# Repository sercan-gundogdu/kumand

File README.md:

# kumand [discontinued*]
Kumand is a low-power user-configurable remote controller device for personal computers, working on WLAN, allowing to manipulate every single media tool that has functionality to operate with keyboard shortcuts/hotkeys by emulating keystrokes determined in selected profile.

*The project is discontinued because the ESP8266 SoC does not meet the project's requirements in the aspect of power consumption and connectivity speed, it seems that ESP8266 has no proper sleep functionality to implement. The project will be redesigned with appropriate connectivity IC and MCU.

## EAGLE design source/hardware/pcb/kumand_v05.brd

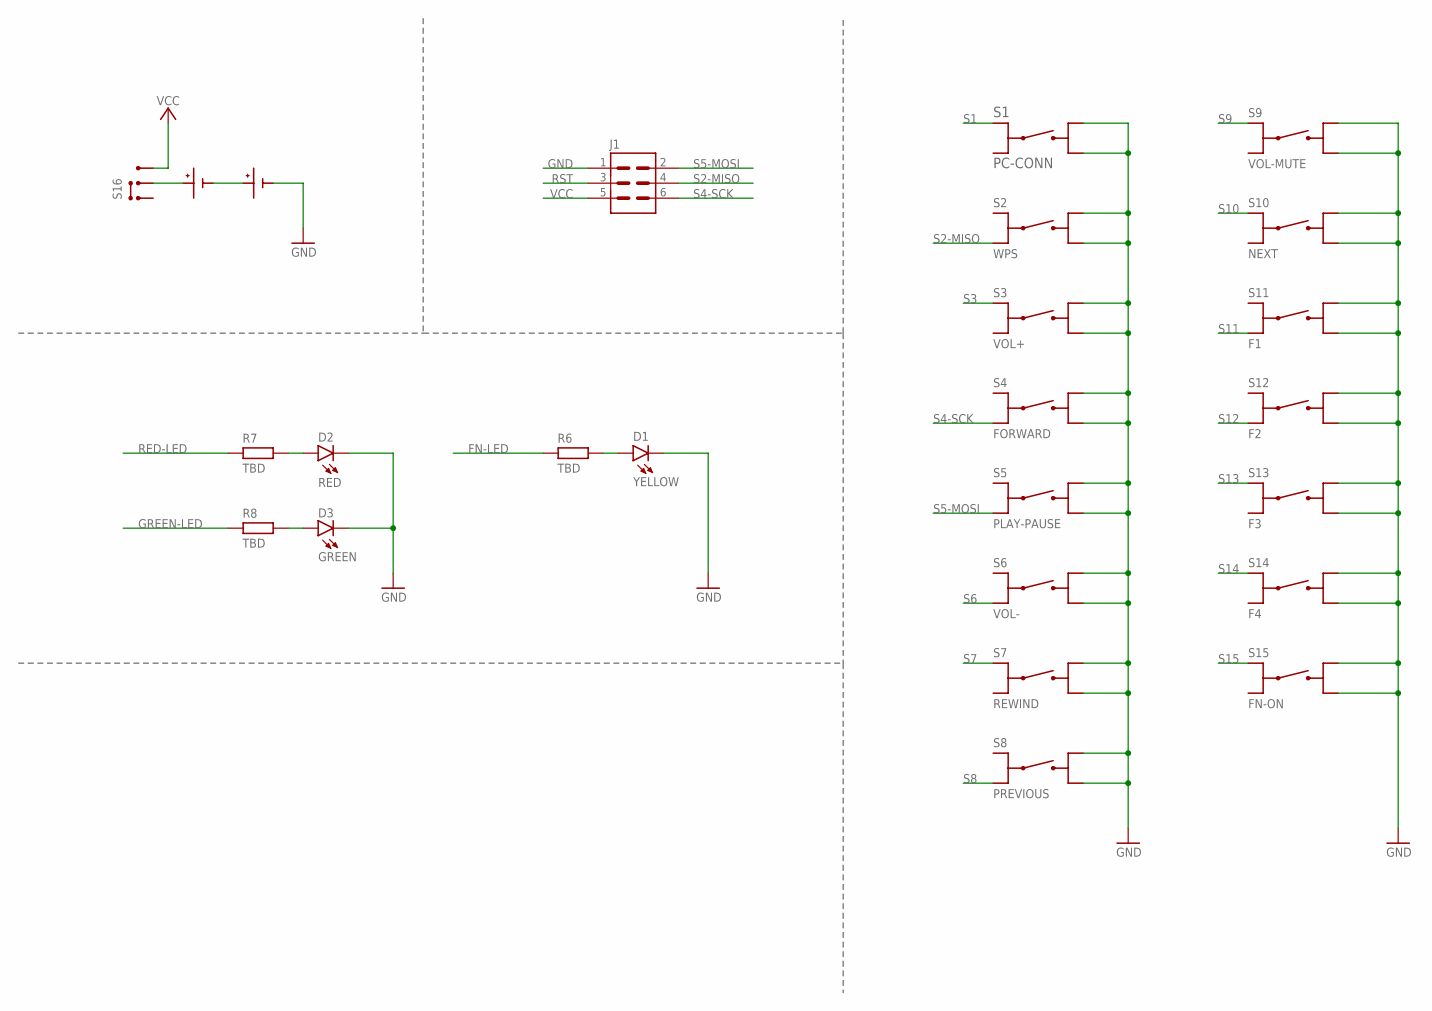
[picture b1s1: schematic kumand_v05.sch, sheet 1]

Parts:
D1: YELLOW; LED-1206
D2: RED; LED-1206
D3: GREEN; LED-1206
J1: 3X2-SMD-DOT
R6, R7, R8: TBD; R1206
S1: PC-CONN; PTS525
S2: WPS; PTS525
S3: VOL+; PTS525
S4: FORWARD; PTS525
S5: PLAY-PAUSE; PTS525
S6: VOL-; PTS525
S7: REWIND; PTS525
S8: PREVIOUS; PTS525
S9: VOL-MUTE; PTS525
S10: NEXT; PTS525
S11: F1; PTS525
S12: F2; PTS525
S13: F3; PTS525
S14: F4; PTS525
S15: FN-ON; PTS525
S16: CL-SB-12B-02T; CL-SB-12B-02T-PACKAGE
U$4, U$5: BK-82-DEVICE; BK-82-PACKAGE

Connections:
FN-LED: R6.2; also elsewhere on the board
GND: D1.C, D2.C, D3.C, J1.1, S1.3, S1.4, S2.3, S2.4, S3.3, S3.4, S4.3, S4.4, S5.3, S5.4, S6.3, S6.4, S7.3, S7.4, S8.3, S8.4, S9.3, S9.4, S10.3, S10.4, S11.3, S11.4, S12.3, S12.4, S13.3, S13.4, S14.3, S14.4, S15.3, S15.4, U$5.P$2, U$5.P$4; also elsewhere on the board
GREEN-LED: R8.2; also elsewhere on the board
unnamed: D1.A, R6.1
unnamed: U$4.P$2, U$4.P$4, U$5.P$1, U$5.P$3
unnamed: S16.P$2, U$4.P$1, U$4.P$3
unnamed: D2.A, R7.1
unnamed: D3.A, R8.1
RED-LED: R7.2; also elsewhere on the board
RST: J1.3; also elsewhere on the board
S1: S1.1; also elsewhere on the board
S2-MISO: J1.4, S2.2; also elsewhere on the board
S3: S3.1; also elsewhere on the board
S4-SCK: J1.6, S4.2; also elsewhere on the board
S5-MOSI: J1.2, S5.2; also elsewhere on the board
S6: S6.2; also elsewhere on the board
S7: S7.1; also elsewhere on the board
S8: S8.2; also elsewhere on the board
S9: S9.1; also elsewhere on the board
S10: S10.1; also elsewhere on the board
S11: S11.2; also elsewhere on the board
S12: S12.2; also elsewhere on the board
S13: S13.1; also elsewhere on the board
S14: S14.1; also elsewhere on the board
S15: S15.1; also elsewhere on the board
VCC: J1.5, S16.P$3; also elsewhere on the board

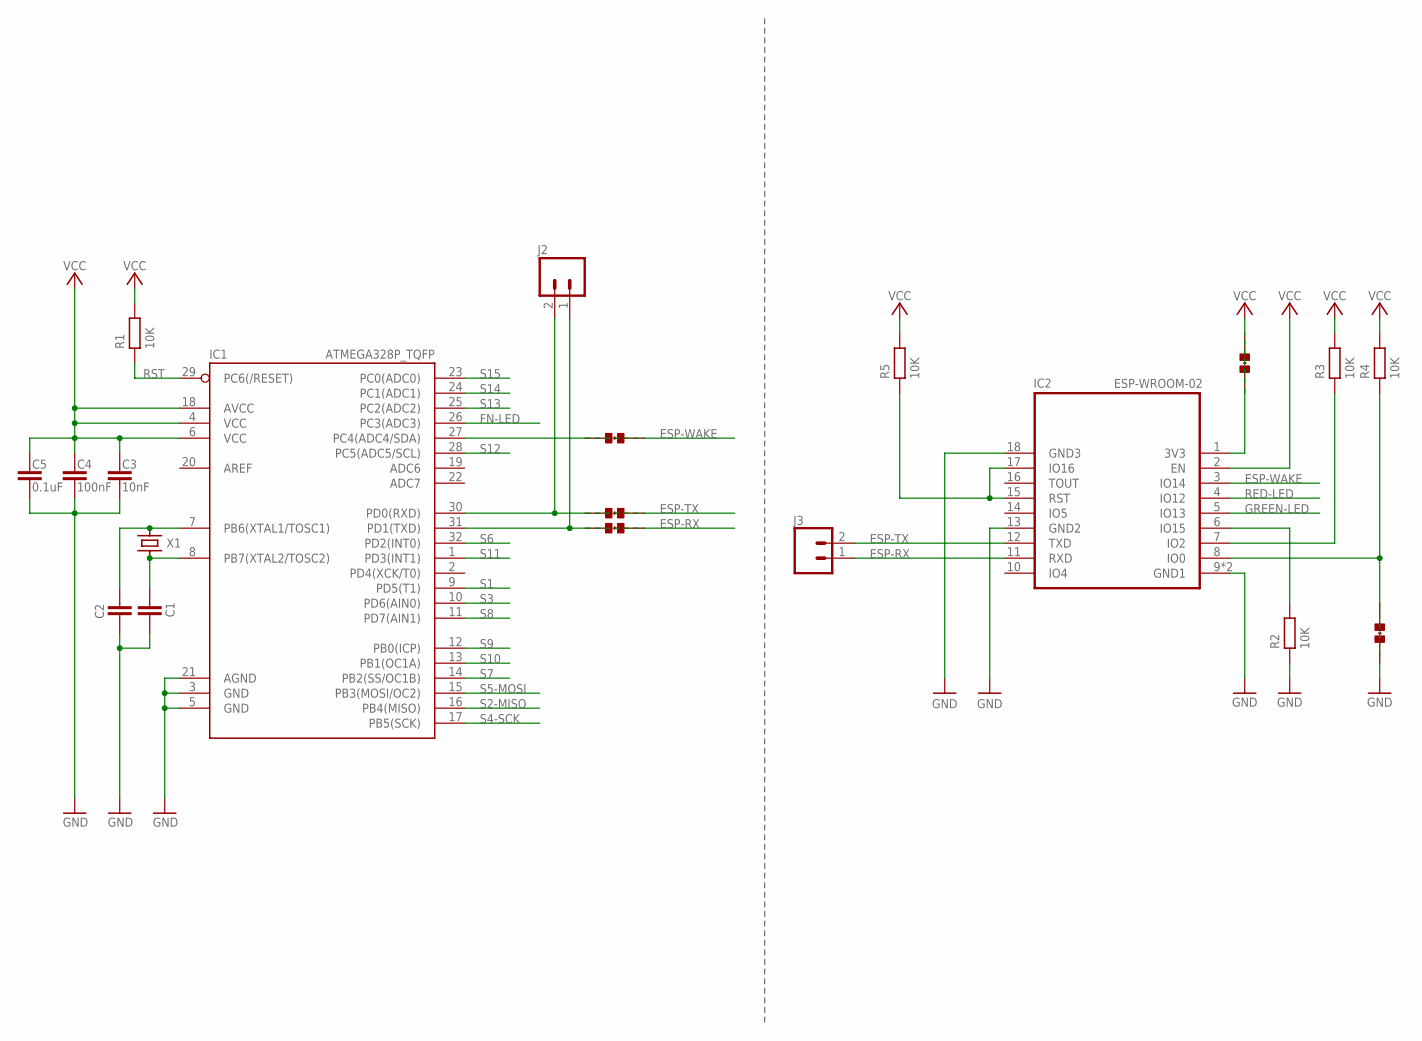
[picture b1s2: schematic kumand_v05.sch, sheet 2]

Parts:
C1, C2: C-EUC1206; C1206
C3: 10nF; C1206
C4: 100nF; C1206
C5: 0.1uF; C1206
IC1: ATMEGA328P_TQFP; TQFP32-08
IC2: ESP-WROOM-02; FRONT-FACE
J2, J3: CONN_02; 1X02
PRG: SOLDER-JUMPER; SOLDER-JUMPER-PACKAGE
R1, R2, R3, R4, R5: 10K; R1206
RX: SOLDER-JUMPER; SOLDER-JUMPER-PACKAGE
TX: SOLDER-JUMPER; SOLDER-JUMPER-PACKAGE
VCC: SOLDER-JUMPER; SOLDER-JUMPER-PACKAGE
WAKE: SOLDER-JUMPER; SOLDER-JUMPER-PACKAGE
X1: NX8045-CRYSTAL; NX8045

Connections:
ESP-IO0: IC2.8 (IO0), PRG.1, R4.1
ESP-IO2: IC2.7 (IO2), R3.1
ESP-IO15: IC2.6 (IO15), R2.1
ESP-RST: IC2.15 (RST), IC2.17 (IO16), R5.2
ESP-RX: IC2.11 (RXD), J3.1, RX.2
ESP-TX: IC2.12 (TXD), J3.2, TX.2
ESP-WAKE: IC2.3 (IO14), WAKE.2
FN-LED: IC1.26 (PC3(ADC3)); also elsewhere on the board
GND: C1.1, C2.1, C3.1, C4.1, C5.1, IC1.3 (GND), IC1.5 (GND), IC1.21 (AGND), IC2.9 (GND1), IC2.13 (GND2), IC2.18 (GND3), IC2.GND (GND1), PRG.2, R2.2; also elsewhere on the board
GREEN-LED: IC2.5 (IO13); also elsewhere on the board
unnamed: C1.2, IC1.8 (PB7(XTAL2/TOSC2)), X1.P$1
unnamed: IC1.27 (PC4(ADC4/SDA)), WAKE.1
unnamed: C2.2, IC1.7 (PB6(XTAL1/TOSC1)), X1.P$2
unnamed: IC1.30 (PD0(RXD)), J2.2, TX.1
unnamed: IC1.31 (PD1(TXD)), J2.1, RX.1
RED-LED: IC2.4 (IO12); also elsewhere on the board
RST: IC1.29 (PC6(/RESET)), R1.2; also elsewhere on the board
S1: IC1.9 (PD5(T1)); also elsewhere on the board
S2-MISO: IC1.16 (PB4(MISO)); also elsewhere on the board
S3: IC1.10 (PD6(AIN0)); also elsewhere on the board
S4-SCK: IC1.17 (PB5(SCK)); also elsewhere on the board
S5-MOSI: IC1.15 (PB3(MOSI/OC2)); also elsewhere on the board
S6: IC1.32 (PD2(INT0)); also elsewhere on the board
S7: IC1.14 (PB2(SS/OC1B)); also elsewhere on the board
S8: IC1.11 (PD7(AIN1)); also elsewhere on the board
S9: IC1.12 (PB0(ICP)); also elsewhere on the board
S10: IC1.13 (PB1(OC1A)); also elsewhere on the board
S11: IC1.1 (PD3(INT1)); also elsewhere on the board
S12: IC1.28 (PC5(ADC5/SCL)); also elsewhere on the board
S13: IC1.25 (PC2(ADC2)); also elsewhere on the board
S14: IC1.24 (PC1(ADC1)); also elsewhere on the board
S15: IC1.23 (PC0(ADC0)); also elsewhere on the board
VCC: C3.2, C4.2, C5.2, IC1.4 (VCC), IC1.6 (VCC), IC1.18 (AVCC), IC2.1 (3V3), IC2.2 (EN), R1.1, R3.2, R4.2, R5.1, VCC.1, VCC.2; also elsewhere on the board

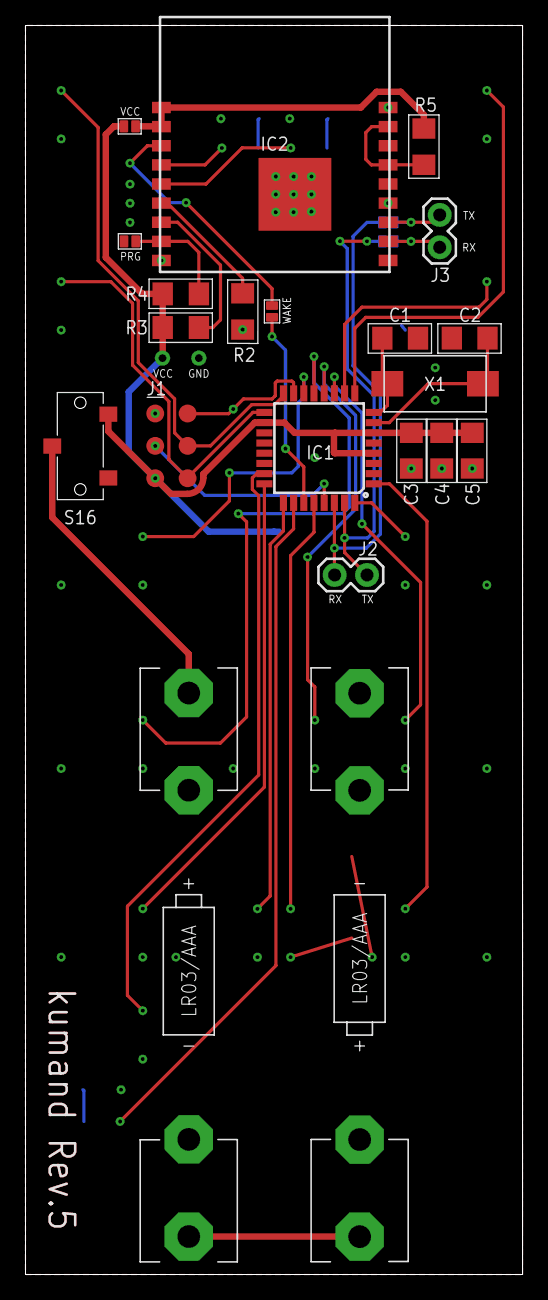
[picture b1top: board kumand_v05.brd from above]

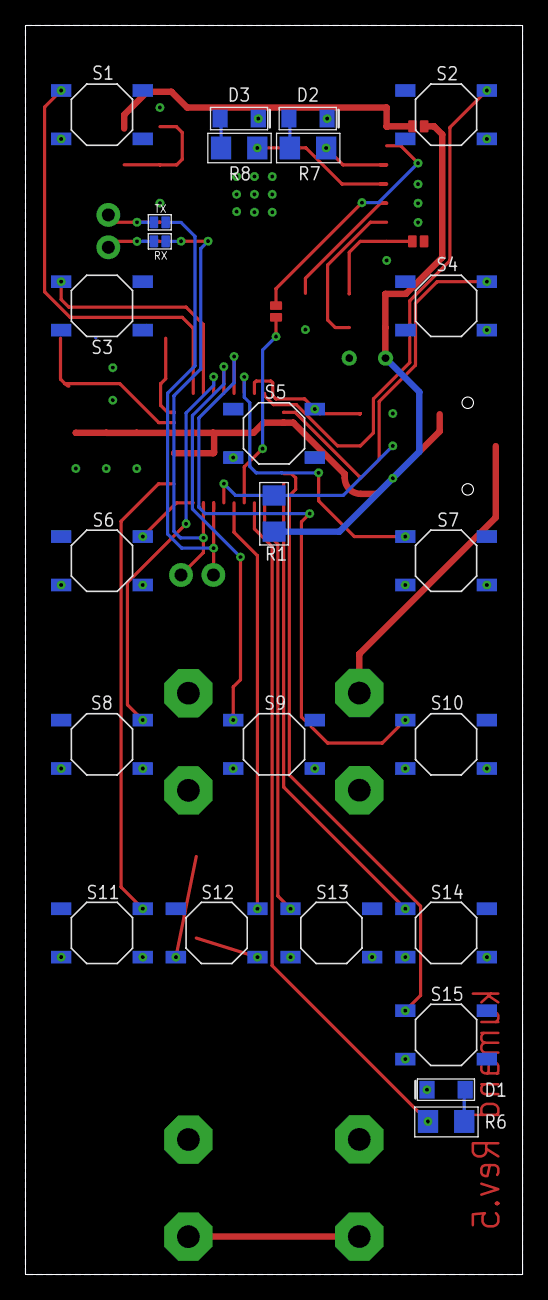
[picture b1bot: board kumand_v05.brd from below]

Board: 2 copper layers, 39.0 x 98.0 mm, 45 parts (24 on the bottom side), 38 nets.

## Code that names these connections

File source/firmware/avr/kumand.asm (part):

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
GPIO_Init:
							// Set PORTB pins 0, 1, 2, 3, 4, 5 as INPUT
							ldi r16, (0<<PB0) | (0<<PB1) | (0<<PB2) | (0<<PB3) | (0<<PB4) | (0<<PB5)
							out DDRB, r16
							
							// Internal pull-up for PORTB pins 0, 1, 2, 3, 4, 5
							ldi r16, (1<<PB0) | (1<<PB1) | (1<<PB2) | (1<<PB3) | (1<<PB4) | (1<<PB5)
							out PORTB, r16
							
							// Set PORTC pins 0, 1, 2, 5 as INPUT
							//	3, 4 as OUTPUT
							ldi r16, (0<<PC0) | (0<<PC1) | (0<<PC2) | (1<<PC3) | (1<<PC4) | (0<<PC5)
							out DDRC, r16
							
							// Internal pull-up for PORTC pins 0, 1, 2, 5
							//	Pins 3,4 driven low
							ldi r16, (1<<PC0) | (1<<PC1) | (1<<PC2) | (0<<PC3) | (0<<PC4) | (1<<PC5) 
							out PORTC, r16
							
							// Set PORTD pins 2, 3, 5, 6, 7 as INPUT
							ldi r16, (0<<PD2) | (0<<PD3) | (0<<PD5) | (0<<PD6) | (0<<PD7)
							out DDRD, r16
							
							// Internal pull-up for PORTD pins 2, 3, 4, 5, 6, 7
							ldi r16, (1<<PD2) | (1<<PD3) | (1<<PD5) | (1<<PD6) | (1<<PD7)
							out PORTD, r16
							
							ret
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
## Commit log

2018-09-30 Label positions are adjusted
2018-09-30 Indent size adjusted
2018-09-30 Added nofile to skeletonise project folders
2018-09-30 Rename folder bat
2018-10-04 Adding Bills of Materials
2019-02-21 Some cosmetic touch to schematic
2019-05-27 cosmetic touch
2019-06-10 rename avr firmware folder
2019-06-10 cosmetic touch on assembly file
2019-06-10 gitignore update
2019-06-10 remove ignored files
2019-09-08 uploading photos of working boards

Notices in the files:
parts and their libraries:
SparkFun-IC-Microcontroller: Licensing: Creative Commons ShareAlike 4.0 International - https://creativecommons.org/licenses/by-sa/4.0
